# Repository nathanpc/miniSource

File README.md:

# miniSource

A portable constant current source.

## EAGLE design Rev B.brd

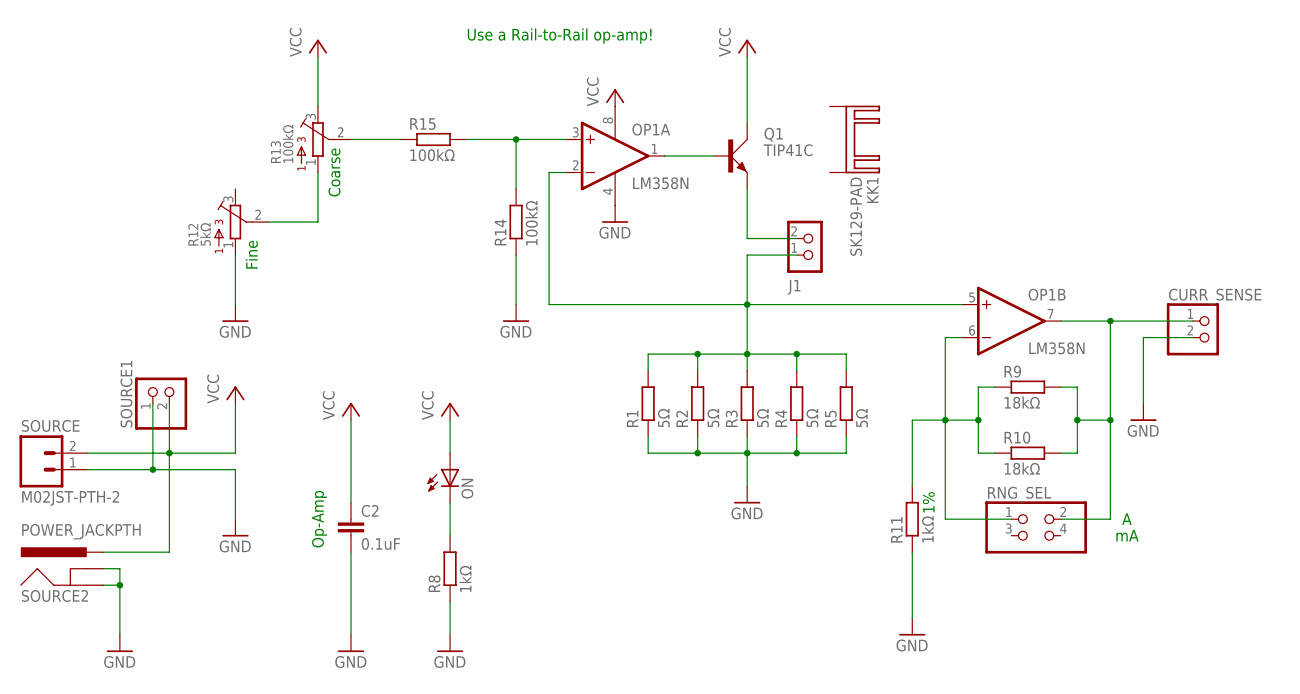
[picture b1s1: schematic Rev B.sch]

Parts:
C2: 0.1uF; C050-025X075
CURR_SENSE: PINHD-1X2; 1X02
J1: CON_TERMINAL_BLOCK_02-5MM; TERMINAL_BLOCK_2P_5
KK1: SK129-PAD; SK129
ON: LEDSQR2X5; LED2X5
OP1: LM358N; DIL08
Q1: TIP41C; TO220AV
R1, R2, R3, R4, R5: 5Ω; P0613/15
R8, R11: 1kΩ; 0207/10
R9, R10: 18kΩ; 0207/10
R12: 5kΩ; 3362U
R13: 100kΩ; 3362U
R14, R15: 100kΩ; 0207/10
RNG_SEL: PINHD-2X2; 2X02
SOURCE: M02JST-PTH-2; JST-2-PTH
SOURCE1: PINHD-1X2; 1X02
SOURCE2: POWER_JACKPTH; POWER_JACK_PTH

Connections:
CURR_SENSE: J1.1, OP1.2 (-IN), OP1.5 (+IN), R1.2, R2.2, R3.2, R4.2, R5.2
GND: C2.2, CURR_SENSE.2, OP1.4 (V-), R1.1, R2.1, R3.1, R4.1, R5.1, R8.1, R11.1, R12.1, R14.1, SOURCE.1, SOURCE1.1, SOURCE2.GND, SOURCE2.GNDBREAK
unnamed: OP1.1 (OUT), Q1.B
unnamed: J1.2, Q1.E
unnamed: R12.2, R13.1
unnamed: OP1.3 (+IN), R14.2, R15.2
unnamed: OP1.6 (-IN), R9.1, R10.1, R11.2, RNG_SEL.1
unnamed: CURR_SENSE.1, OP1.7 (OUT), R9.2, R10.2, RNG_SEL.2
unnamed: R13.2, R15.1
unnamed: ON.K (C), R8.2
VCC: C2.1, ON.A, OP1.8 (V+), Q1.C, R13.3, SOURCE.2, SOURCE1.2, SOURCE2.PWR

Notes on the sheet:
Op-Amp
Fine
Coarse
Use a Rail-to-Rail op-amp!

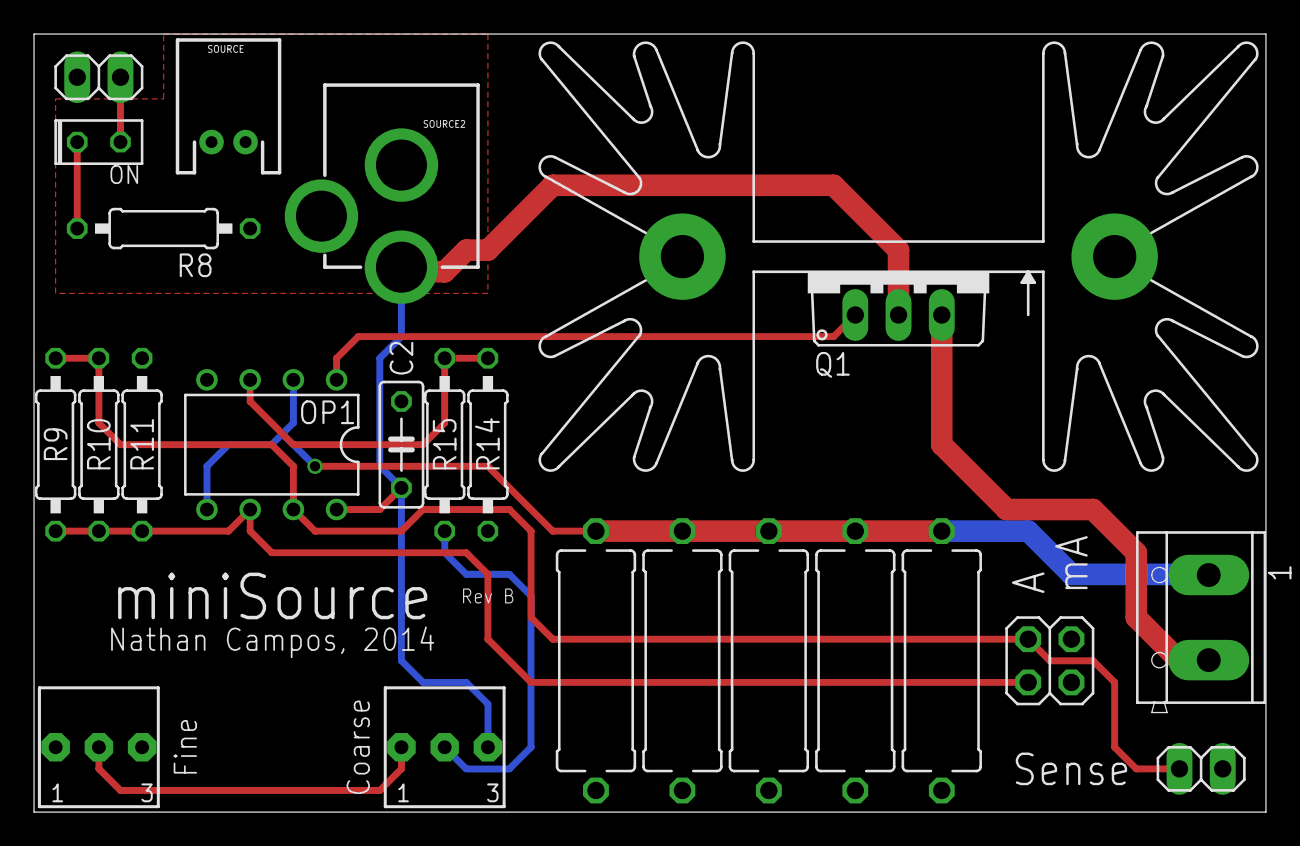
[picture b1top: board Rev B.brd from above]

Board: 4 copper layers, 72.4 x 45.7 mm, 24 parts (0 on the bottom side), 11 nets.

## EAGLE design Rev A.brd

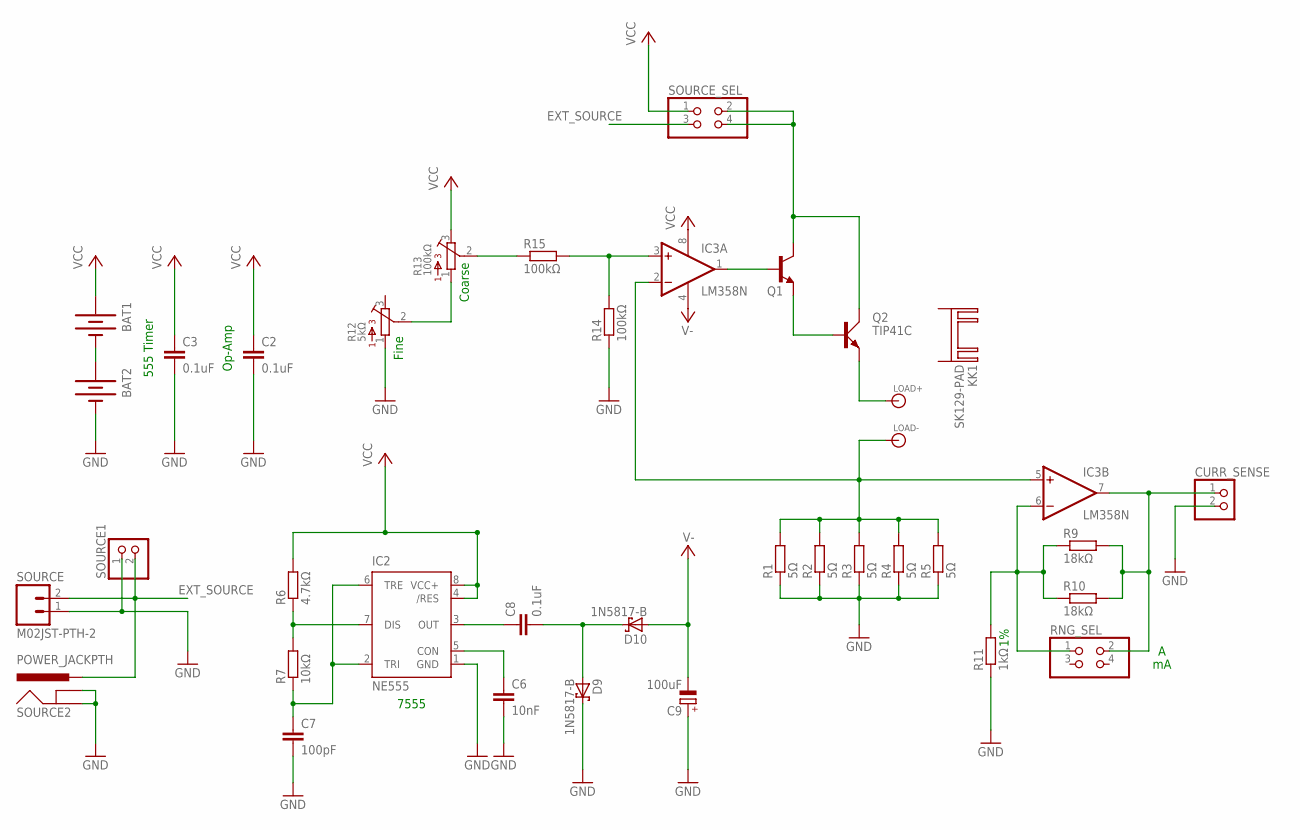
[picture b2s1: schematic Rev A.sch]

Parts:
BAT1, BAT2: BATTERYAA; BATTERY-AA
C2, C3, C8: 0.1uF; C050-025X075
C6: 10nF; C050-025X075
C7: 100pF; C025-025X050
C9: 100uF; E2,5-6
CURR_SENSE: PINHD-1X2; 1X02
D9, D10: 1N5817-B; DO41-7.6
IC2: NE555; DIL-08
IC3: LM358N; DIL08
KK1: SK129-PAD; SK129
LOAD+: BANANA_CONN
LOAD-: BANANA_CONN
Q1: 2N5551-NPN-TO92-CBE; TO92-CBE
Q2: TIP41C; TO220AV
R1, R2, R3, R4, R5: 5Ω; P0613/15
R6: 4.7kΩ; 0207/10
R7: 10kΩ; 0207/10
R9, R10: 18kΩ; 0207/10
R11: 1kΩ; 0207/10
R12: 5kΩ; 3362U
R13: 100kΩ; 3362U
R14, R15: 100kΩ; 0207/10
RNG_SEL: PINHD-2X2; 2X02
SOURCE: M02JST-PTH-2; JST-2-PTH
SOURCE1: PINHD-1X2; 1X02
SOURCE2: POWER_JACKPTH; POWER_JACK_PTH
SOURCE_SEL: PINHD-2X2; 2X02

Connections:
CURR_SENSE: IC3.2 (-IN), IC3.5 (+IN), LOAD-.P$1, R1.2, R2.2, R3.2, R4.2, R5.2
EXT_SOURCE: SOURCE.2, SOURCE1.2, SOURCE2.PWR, SOURCE_SEL.3
GND: BAT2.GND@1 (-), C2.2, C3.2, C6.2, C7.2, C9.+, CURR_SENSE.2, D9.C, IC2.1 (GND), R1.1, R2.1, R3.1, R4.1, R5.1, R11.1, R12.1, R14.1, SOURCE.1, SOURCE1.1, SOURCE2.GND, SOURCE2.GNDBREAK
unnamed: IC3.1 (OUT), Q1.B
unnamed: Q1.E, Q2.B
unnamed: Q1.C, Q2.C, SOURCE_SEL.2, SOURCE_SEL.4
unnamed: LOAD+.P$1, Q2.E
unnamed: R12.2, R13.1
unnamed: IC3.3 (+IN), R14.2, R15.2
unnamed: IC3.6 (-IN), R9.1, R10.1, R11.2, RNG_SEL.1
unnamed: CURR_SENSE.1, IC3.7 (OUT), R9.2, R10.2, RNG_SEL.2
unnamed: BAT1.GND@1 (-), BAT2.PWR@1 (+)
unnamed: R13.2, R15.1
unnamed: C8.1, IC2.3 (OUT)
unnamed: C6.1, IC2.5 (CON)
unnamed: C7.1, IC2.2 (TRI), IC2.6 (TRE), R7.1
unnamed: IC2.7 (DIS), R6.1, R7.2
unnamed: C8.2, D9.A, D10.C
V-: C9.-, D10.A, IC3.4 (V-)
VCC: BAT1.PWR@1 (+), C2.1, C3.1, IC2.4 (/RES), IC2.8 (VCC+), IC3.8 (V+), R6.2, R13.3, SOURCE_SEL.1

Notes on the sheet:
555 Timer
Op-Amp
Fine
Coarse
7555

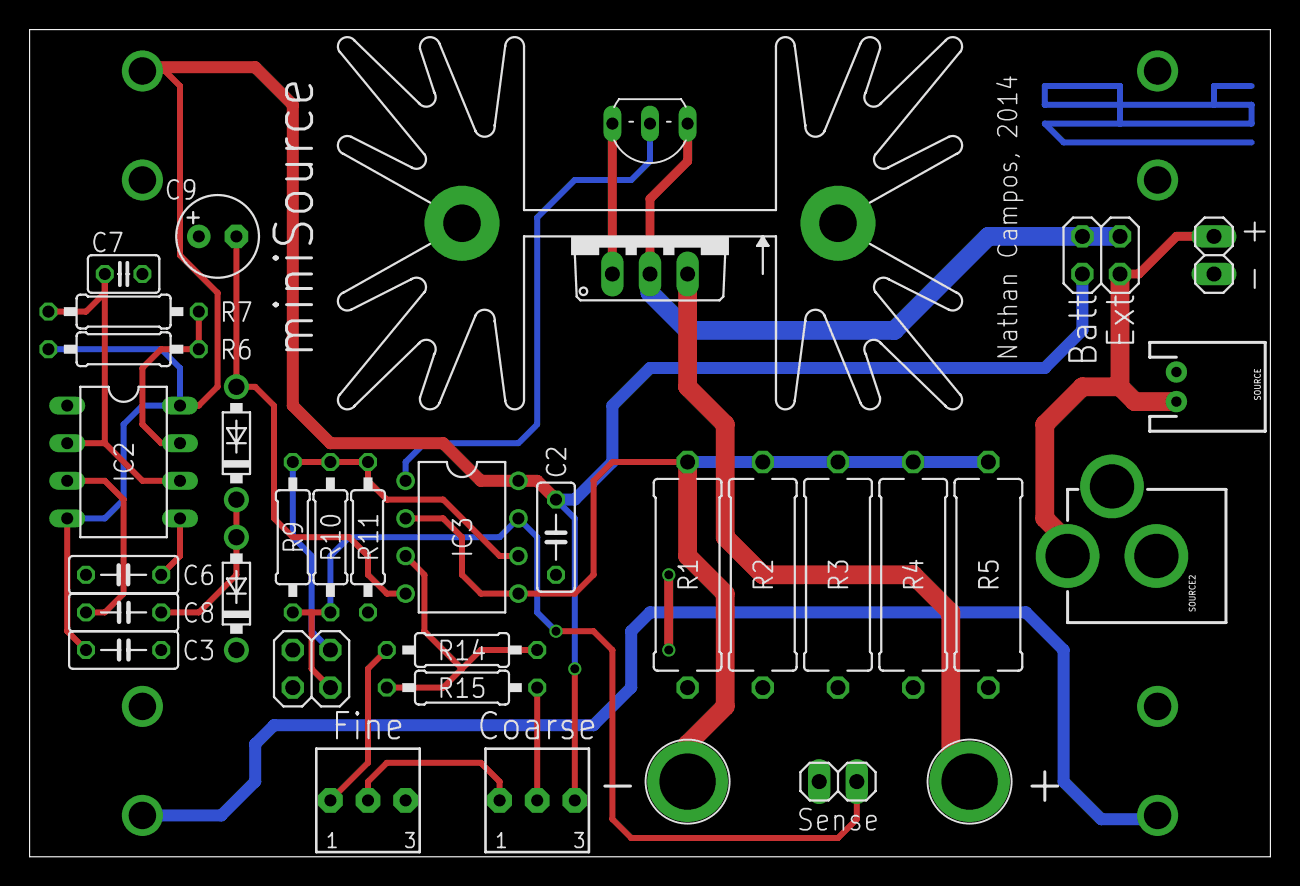
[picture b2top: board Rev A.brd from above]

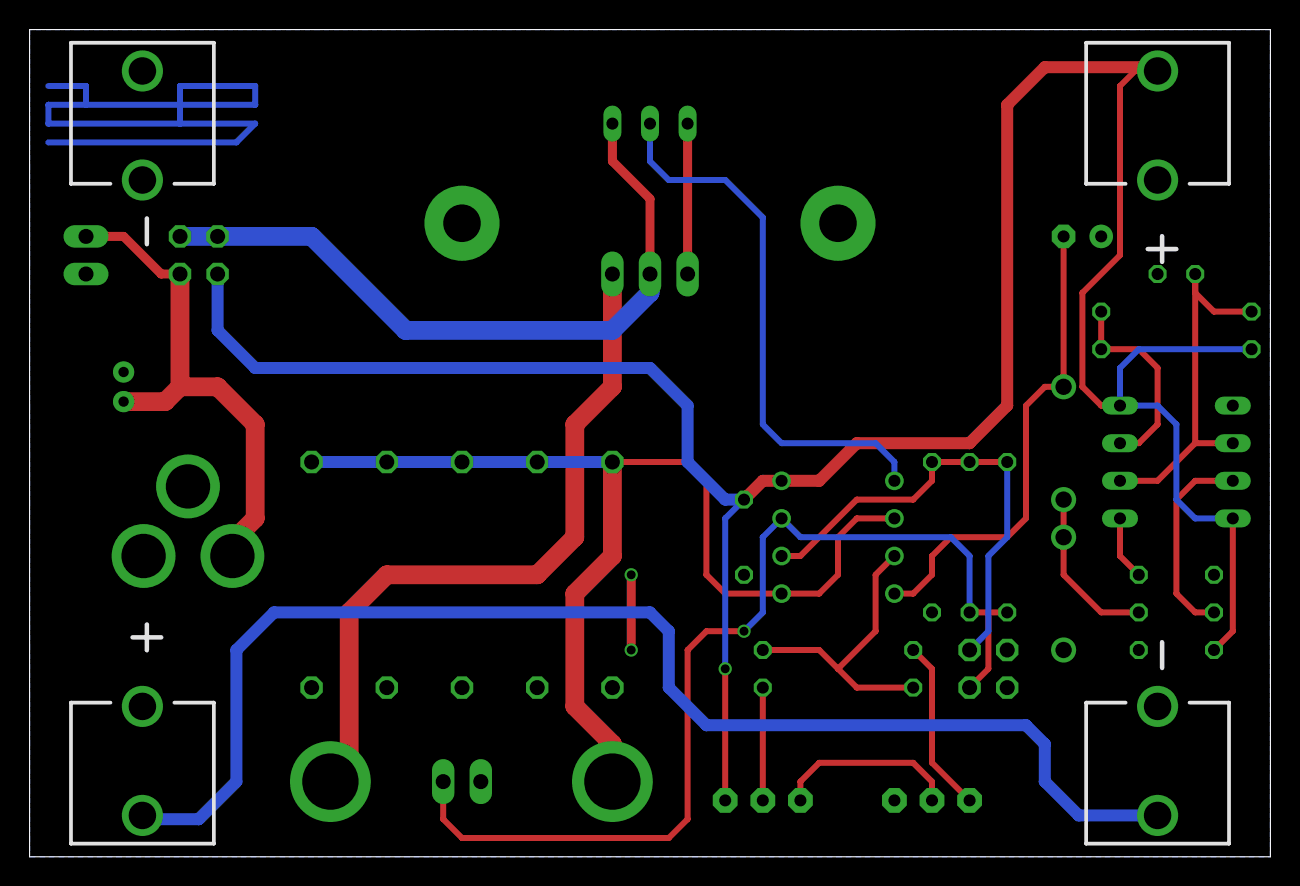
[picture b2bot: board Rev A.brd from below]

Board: 4 copper layers, 83.8 x 55.9 mm, 37 parts (2 on the bottom side), 20 nets.

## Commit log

2014-01-09 Main part of the circuit in place
2014-01-09 Finished the schematic
2014-01-09 Started laying out the board
2014-01-09 Made some little fixes to the schematic
2014-01-09 Finished the layout
2014-01-09 Gerbers
2014-01-11 Exported the schematic and board layout
2014-01-11 Fixed the embedded images
2014-03-13 Rev B

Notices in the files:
parts and their libraries:
SparkFun-Connectors: Licensing: CC v3.0 Share-Alike You are welcome to use this library for commercial purposes.
